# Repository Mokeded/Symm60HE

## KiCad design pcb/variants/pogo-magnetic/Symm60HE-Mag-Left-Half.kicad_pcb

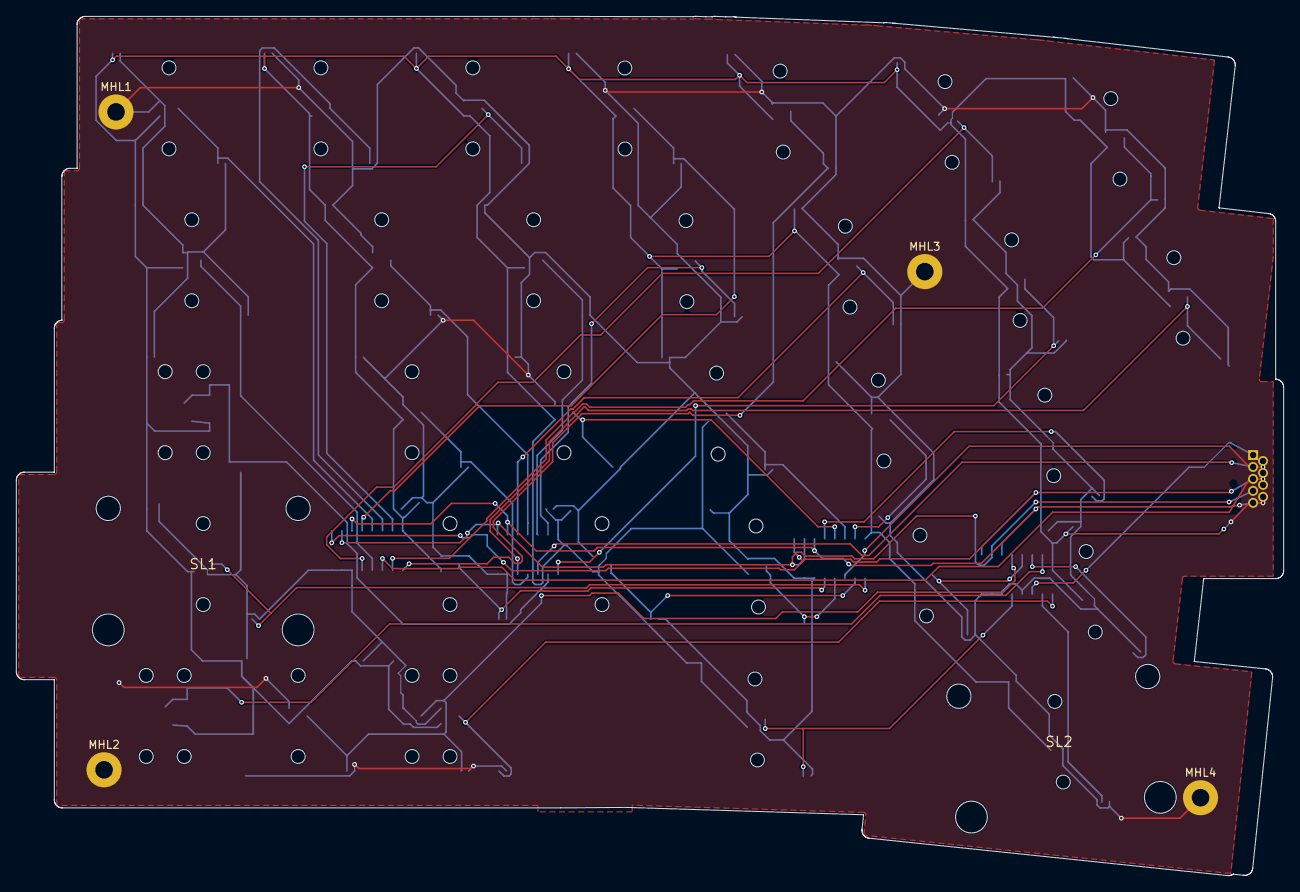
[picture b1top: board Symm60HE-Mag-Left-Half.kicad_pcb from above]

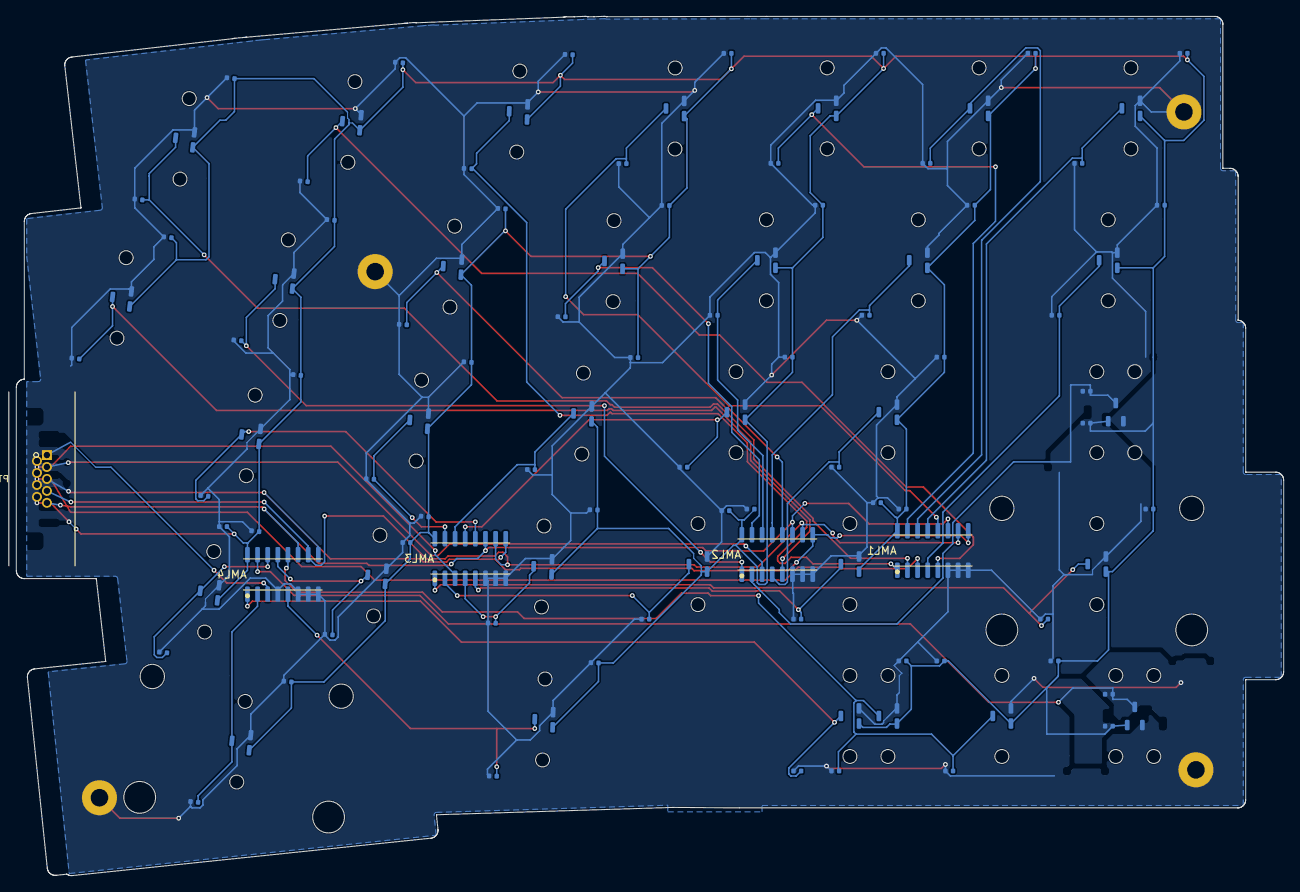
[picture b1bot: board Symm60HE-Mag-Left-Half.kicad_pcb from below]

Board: 2 copper layers, 158.9 x 107.8 mm, 115 parts (109 on the bottom side), 40 nets.

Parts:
AML1, AML2, AML3, AML4: SN74LV4051A; AM1_SOIC-16_3.9x9.9mm_P1.27mm
CL1A, CL2A, CL3A, CL4A, CL5A, CL6A, CL7A, CL8A, CL9A, CL10A, CL11A, CL12A, CL13A, CL14A, CL15A, CL16A, CL17A, CL18A, CL19A, CL20A, CL21A, CL22A, CL23A, CL24A, CL25A, CL26A, CL27A, CL29A, CL30A, CL31A, CL32A, CL33A: 100n; C1_C_0402_1005Metric
CL1B, CL2B, CL3B, CL4B, CL5B, CL6B, CL7B, CL8B, CL9B, CL10B, CL11B, CL12B, CL13B, CL14B, CL15B, CL16B, CL17B, CL18B, CL19B, CL20B, CL21B, CL22B, CL23B, CL24B, CL25B, CL26B, CL27B, CL29B, CL30B, CL31B, CL32B, CL33B: 4.7n; C1_C_0402_1005Metric
CML1, CML2, CML3, CML4: 100n; C1_C_0402_1005Metric
HEL1, HEL2, HEL3, HEL4, HEL5, HEL6, HEL7, HEL9, HEL10, HEL11, HEL12, HEL13, HEL14, HEL16, HEL17, HEL18, HEL19, HEL20, HEL22, HEL23, HEL24, HEL25, HEL26, HEL29, HEL31: MT9102ET; HE_KEY_1.00u
HEL8, HEL30, HEL32: MT9102ET; HE_KEY_1.50u
HEL15, HEL27: MT9102ET; HE_SHARED_MIDPOINT
HEL21, HEL33: MT9102ET; HE_KEY_2.25u
KML15N, KML15S, KML27A, KML27N: MX_MECHANICAL_ONLY; HE_KEY_MECHANICAL_ONLY
MHL1, MHL2, MHL3, MHL4: M2; MountingHole_2.2mm_M2_Pad
PTL1: 904-00080; MagPogo_9_MC142_Target
SL1, SL2: STAB_MX; STABILIZER_MX_2U

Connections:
+3V3A: AML1.16, AML2.16, AML3.16, AML4.16, CL1A.1, CL2A.1, CL3A.1, CL4A.1, CL5A.1, CL6A.1, CL7A.1, CL8A.1, CL9A.1, CL10A.1, CL11A.1, CL12A.1, CL13A.1, CL14A.1, CL15A.1, CL16A.1, CL17A.1, CL18A.1, CL19A.1, CL20A.1, CL21A.1, CL22A.1, CL23A.1, CL24A.1, CL25A.1, CL26A.1, CL27A.1, CL29A.1, CL30A.1, CL31A.1, CL32A.1, CL33A.1, CML1.1, CML2.1, CML3.1, CML4.1, HEL1.1, HEL2.1, HEL3.1, HEL4.1, HEL5.1, HEL6.1, HEL7.1, HEL8.1, HEL9.1, HEL10.1, HEL11.1, HEL12.1, HEL13.1, HEL14.1, HEL15.1, HEL16.1, HEL17.1, HEL18.1, HEL19.1, HEL20.1, HEL21.1, HEL22.1, HEL23.1, HEL24.1, HEL25.1, HEL26.1, HEL27.1, HEL29.1, HEL30.1, HEL31.1, HEL32.1, HEL33.1, PTL1.9
ADC_L1: AML1.3, PTL1.7
ADC_L2: AML2.3, PTL1.2
ADC_L3: AML3.3, PTL1.6
ADC_L4: AML4.3, PTL1.1
GND: AML1.6, AML1.7, AML1.8, AML2.6, AML2.7, AML2.8, AML3.6, AML3.7, AML3.8, AML4.4, AML4.6, AML4.7, AML4.8, CL1A.2, CL1B.2, CL2A.2, CL2B.2, CL3A.2, CL3B.2, CL4A.2, CL4B.2, CL5A.2, CL5B.2, CL6A.2, CL6B.2, CL7A.2, CL7B.2, CL8A.2, CL8B.2, CL9A.2, CL9B.2, CL10A.2, CL10B.2, CL11A.2, CL11B.2, CL12A.2, CL12B.2, CL13A.2, CL13B.2, CL14A.2, CL14B.2, CL15A.2, CL15B.2, CL16A.2, CL16B.2, CL17A.2, CL17B.2, CL18A.2, CL18B.2, CL19A.2, CL19B.2, CL20A.2, CL20B.2, CL21A.2, CL21B.2, CL22A.2, CL22B.2, CL23A.2, CL23B.2, CL24A.2, CL24B.2, CL25A.2, CL25B.2, CL26A.2, CL26B.2, CL27A.2, CL27B.2, CL29A.2, CL29B.2, CL30A.2, CL30B.2, CL31A.2, CL31B.2, CL32A.2, CL32B.2, CL33A.2, CL33B.2, CML1.2, CML2.2, CML3.2, CML4.2, HEL1.2, HEL2.2, HEL3.2, HEL4.2, HEL5.2, HEL6.2, HEL7.2, HEL8.2, HEL9.2, HEL10.2, HEL11.2, HEL12.2, HEL13.2, HEL14.2, HEL15.2, HEL16.2, HEL17.2, HEL18.2, HEL19.2, HEL20.2, HEL21.2, HEL22.2, HEL23.2, HEL24.2, HEL25.2, HEL26.2, HEL27.2, HEL29.2, HEL30.2, HEL31.2, HEL32.2, HEL33.2, MHL1.1, MHL2.1, MHL3.1, MHL4.1, PTL1.8
HE_L01: AML1.13, CL1B.1, HEL1.3
HE_L02: AML1.14, CL2B.1, HEL2.3
HE_L03: AML1.15, CL3B.1, HEL3.3
HE_L04: AML1.12, CL4B.1, HEL4.3
HE_L05: AML1.1, CL5B.1, HEL5.3
HE_L06: AML1.5, CL6B.1, HEL6.3
HE_L07: AML1.2, CL7B.1, HEL7.3
HE_L08: AML1.4, CL8B.1, HEL8.3
HE_L09: AML2.13, CL9B.1, HEL9.3
HE_L10: AML2.14, CL10B.1, HEL10.3
HE_L11: AML2.15, CL11B.1, HEL11.3
HE_L12: AML2.12, CL12B.1, HEL12.3
HE_L13: AML2.1, CL13B.1, HEL13.3
HE_L14: AML2.5, CL14B.1, HEL14.3
HE_L15: AML2.2, CL15B.1, HEL15.3
HE_L16: AML2.4, CL16B.1, HEL16.3
HE_L17: AML3.13, CL17B.1, HEL17.3
HE_L18: AML3.14, CL18B.1, HEL18.3
HE_L19: AML3.15, CL19B.1, HEL19.3
HE_L20: AML3.12, CL20B.1, HEL20.3
HE_L21: AML3.1, CL21B.1, HEL21.3
HE_L22: AML3.5, CL22B.1, HEL22.3
HE_L23: AML3.2, CL23B.1, HEL23.3
HE_L24: AML3.4, CL24B.1, HEL24.3
HE_L25: AML4.13, CL25B.1, HEL25.3
HE_L26: AML4.14, CL26B.1, HEL26.3
HE_L27: AML4.15, CL27B.1, HEL27.3
HE_L28: AML4.12, CL29B.1, CL30B.1, HEL29.3, HEL30.3
HE_L29: AML4.1, CL31B.1, HEL31.3
HE_L30: AML4.5, CL32B.1, HEL32.3
HE_L31: AML4.2, CL33B.1, HEL33.3
MUX_A0: AML1.11, AML2.11, AML3.11, AML4.11, PTL1.5
MUX_A1: AML1.10, AML2.10, AML3.10, AML4.10, PTL1.4
MUX_A2: AML1.9, AML2.9, AML3.9, AML4.9, PTL1.3

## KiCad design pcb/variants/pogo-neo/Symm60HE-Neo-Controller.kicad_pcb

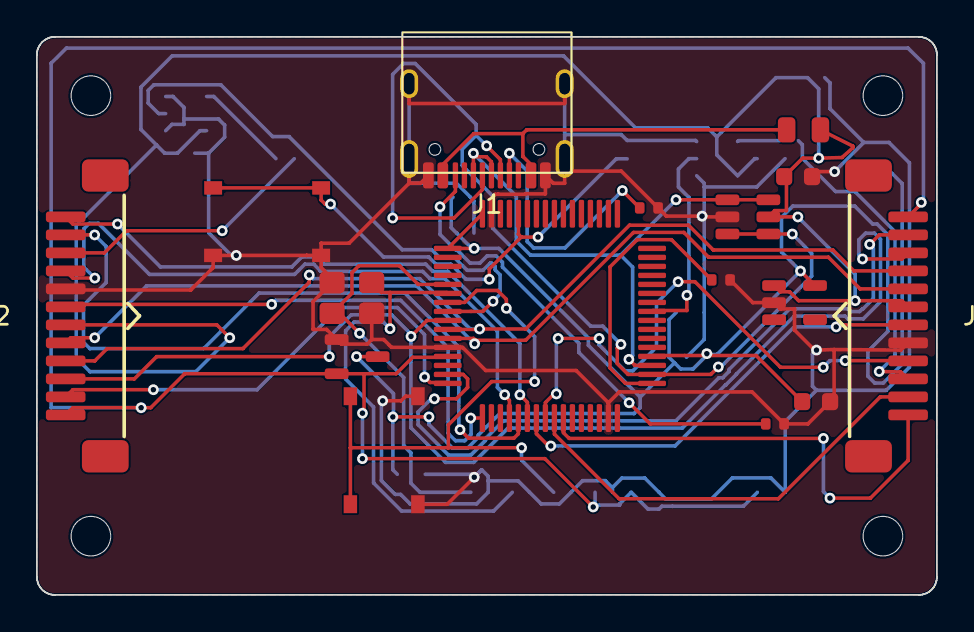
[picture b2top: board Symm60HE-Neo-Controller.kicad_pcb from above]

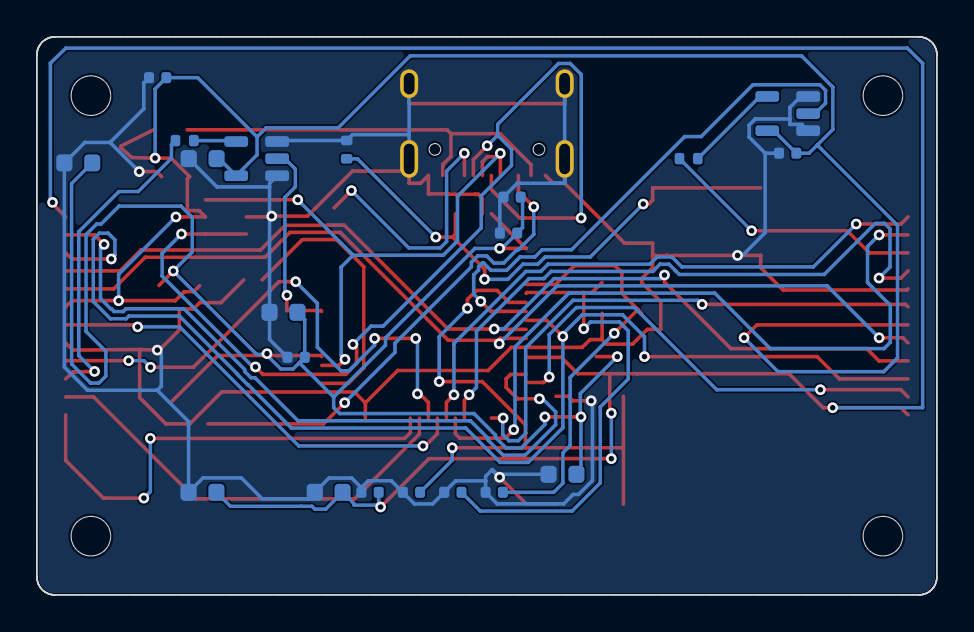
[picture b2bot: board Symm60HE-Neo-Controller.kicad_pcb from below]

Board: 2 copper layers, 50.0 x 31.0 mm, 40 parts (20 on the bottom side), 33 nets.

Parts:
C1, C8: 10u; C148_C_0603_1608Metric
C2, C10: 1u; C148_C_0603_1608Metric
C3, C4: 30p; C1_C_0402_1005Metric
C5, C6, C7, C9, C11, C16, C17: 100n; C1_C_0402_1005Metric
C12, C13, C14, C15: 2.2u; C148_C_0603_1608Metric
F1: 0.5A; F1_Fuse_0805_2012Metric
J1: TYPE-C-31-M-12; USB_C_Receptacle_HRO_TYPE-C-31-M-12
J2, J3: FFC_12P; FFC_12P_1.00mm_TopContact
MHD1, MHD2, MHD3, MHD4: M2_NPTH; MountingHole_2.2mm_M2_NPTH
R1, R4: 12k; R3_R_0402_1005Metric
R2, R3: 5.1k; R3_R_0402_1005Metric
R5, R6: 470R; R3_R_0402_1005Metric
SW1, SW2: TS-1187A; SW1_SW_Push_1P1T_XKB_TS-1187A
U1: AT32F405RCT7; U4_LQFP-64_10x10mm_P0.5mm
U2: USBLC6-2SC6; U1_SOT-23-6
U3: TLV75733PDBV; U2_SOT-23-5
U4: XC6206P332MR; U3_SOT-23-3
U5, U6: SN74AHCT1G125; U2_SOT-23-5
Y1: 12MHz; Y1_Crystal_SMD_3225-4Pin_3.2x2.5mm

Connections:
+3V3A: C9.1, C10.1, C15.1, J2.1, J3.1, U1.13, U4.2
+3V3D: C2.1, C5.1, C6.1, C7.1, C8.1, C13.1, C14.1, U1.1, U1.36, U1.64, U3.5, U4.3
ADC_L1: J2.7, U1.17
ADC_L2: J2.9, U1.20
ADC_L3: J2.11, U1.21
ADC_L4: J2.12, U1.22
ADC_L5: J2.2, U1.16
ADC_R1: J3.7, U1.23
ADC_R2: J3.9, U1.24
ADC_R3: J3.11, U1.25
ADC_R4: J3.12, U1.26
ADC_R5: J3.2, U1.15
BOOT0: R4.1, SW1.1, U1.60
CC1: J1.A5, R2.1
CC2: J1.B5, R3.1
GND: C1.2, C2.2, C3.2, C4.2, C5.2, C6.2, C7.2, C8.2, C9.2, C10.2, C11.2, C12.2, C13.2, C14.2, C15.2, C16.2, C17.2, J1.A1, J1.A12, J1.B1, J1.B12, J1.SH, J2.8, J3.8, R1.2, R2.2, R3.2, R4.2, SW1.2, SW2.2, U1.12, U1.31, U1.63, U2.2, U3.2, U4.1, U5.1, U5.3, U6.1, U6.3, Y1.2, Y1.4
MUX_A0: J2.3, J3.3, U1.9
MUX_A1: J2.4, J3.4, U1.10
MUX_A2: J2.5, J3.5, U1.11
NRST: C11.1, SW2.1, U1.7
RGB_L: J2.10, R5.2
RGB_L_BUF: R5.1, U5.4
RGB_L_MCU: U1.8, U5.2
RGB_R: J3.10, R6.2
RGB_R_BUF: R6.1, U6.4
RGB_R_MCU: U1.41, U6.2
USB_DM: J1.A7, J1.B7, U1.34, U2.3, U2.4
USB_DP: J1.A6, J1.B6, U1.35, U2.1, U2.6
USB_R: R1.1, U1.33
VBUS: C1.1, C12.1, C16.1, C17.1, F1.2, J2.6, J3.6, U2.5, U3.1, U5.5, U6.5
VBUS_IN: F1.1, J1.A4, J1.A9, J1.B4, J1.B9
XTAL_IN: C3.1, U1.5, Y1.1
XTAL_OUT: C4.1, U1.6, Y1.3
